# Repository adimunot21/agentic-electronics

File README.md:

# agentic-electronics

An experiment in letting an AI agent change an electronic circuit design, while an independent checker decides whether each change is accepted.

The agent proposes small edits to a parts list. It never judges its own work. A separate evaluator re-runs the real simulations (ngspice, KiCad) on the edited design and accepts or rejects the change against a policy written beforehand. The test circuit is an analog anti-aliasing filter in front of a 12-bit ADC.

This is research code. Nothing here is a board ready to manufacture.

## Status

Newest first. New entries are added on top; old entries are not rewritten.

* **2026-11-21. improve-live-12: ACCEPTED (v4).** After two honest no-improvement declarations the agent submitted one design that the independent evaluator accepted for the objective (alias -58.74 -> -59.58 dB, no policy violations; E96/E24 values, part numbers still unverified, REQ-STAB/REQ-BOM failures pre-existing). One accepted run in four on v4; advisory aids were visible (docs sections 25-26).
* **2026-11-21. improve-live-10 and v4 attainability.** Run 10 declared no improvement after reading its own previews (honest, not accepted). An offline search showed policy v4 is attainable (designs withheld from the repo). The advisory sanity check now also predicts REQ-BIAS; digest superseded with proof (docs sections 23-24).
* **2026-11-21. improve-live-9: no evaluation.** The agent spent all 45 model calls on 21 patches and 17 free sanity checks and never submitted (a usage limit hit mid-run and the new supervisor resumed it). Not accepted. Fix: the agent now sees its call budget in every reply; acceptance and policies unchanged. Digest superseded with proof (docs section 22).
* **2026-11-21. Pre-trial freeze.** README task labels, restoration-mode check list and E96 alias coverage for the advisory sanity check are done; trusted digest superseded with proof (docs section 21). Next: a live v4 trial under the hardened harness.
* **2026-11-20. Second-circuit groundwork.** A circuit-profile seam lets a second task be added by data (FE-AAF-001 behaviour unchanged), a supervisor resumes runs after provider usage limits, advisory edit-sanity is validated on 11 real designs, and a capacitor orderability table exists. A second-circuit contract is only a draft awaiting owner approval and is not published.
* **2026-11-20. Backlog 1-3 shipped by a five-agent hierarchy.** Provider usage limits are now their own stop reason (reset time recorded, preview budget kept across resume, `--wait-until-reset`); one combined preview covers corners plus guarded nominal metrics; an advisory edit-sanity check predicts corner gain before an evaluation is spent. Orderability research is partial (capacitor ranges unsourced). 346 unit + 14 integration tests pass; trusted digest superseded with proof (docs section 18).
* **2026-11-20. Public CI fixed.** The integration job had been failing since the first public push because the tool containers run as user 1000 and a GitHub runner is user 1001, so they could not write to the checkout. The repository now opens its own work directories for the containers; the latest run on `main` is green (unit and integration). New trusted digest recorded in the docs.
* **2026-11-20. Eighth live run: two evaluations, both rejected, then my subscription's usage limit.** The model found a design inside every corner limit with 0.54 dB of improvement (target 0.5), but a bias-margin rule it had not previewed rejected it; its repair broke the gain window. Runs 7 and 8 were cut short by the plan limit as much as by the design problem. Next on the backlog: handle provider limits automatically, and preview all guarded metrics together.
* **2026-11-20. Seventh live run (fourth task version): no evaluation reached, nothing accepted.** The new standard-values check worked (the model was refused four times for non-standard resistor values and adapted), but the run was interrupted by my subscription's usage limit, resumed once, and then stopped on three scattered malformed replies. The malformed-reply rule is now three in a row (twelve in total) instead of three in total. Tests pass (253 unit, 14 integration). New digest recorded in the docs.
* **2026-11-20. Orderable-values check added; fourth task version frozen.** The accepted design from run 6 used a resistor value (59.6k) that is not a standard 1% value, so it was not buildable. The edit checker can now refuse values outside the part's declared standard series (E96 resistors, E24 capacitors); task `improve-wide-retune-alias-v4` turns that on and is otherwise the same task. Tests pass (253 unit, 14 integration). New trusted digest recorded in the docs. No run on v4 yet.
* **2026-11-20. Fifth/sixth live runs: first acceptance on a task with no scripted answer** (`runs/agent/improve-live-6`; run 5 was lost to a provider timeout). The model used the worst-case and requirement previews, was rejected once for a tiny stability-metric increase, and was then accepted: worst-case stopband rejection improved by 1.0 dB (target 0.5 dB) by changing two parts (R1 59k to 59.6k, C1 18n to 20n). The run was interrupted by my subscription's 5-hour usage limit and resumed once. Limits: the new values are not orderable as far as I could check (59.6k is not a standard 1% value, and neither part number was found at the distributor searched), so this is not a buildable design; REQ-STAB is still failed; one task, advisory previews used, model may know this circuit class.
* **2026-11-20. Fourth live run: closest so far, nothing accepted** (`runs/agent/improve-live-4`). With the new worst-case preview the model found designs that beat the 0.5 dB target by about 1.8 dB inside every tolerance corner, but the stability check (REQ-STAB, which must not get worse) rejected both submissions, and the run hit its 30-call cap before the model could act on the second rejection. Added a second advisory preview that shows the nominal value of every requirement, including REQ-STAB, before a submission. Tests pass (218 unit, 14 integration). One run, one task.
* **2026-11-20. Harness milestones 1 and 2 landed; no new live run yet.** Duplicates and no-ops are now detected by the circuit's electrical content, not by file bytes, so a reverted design costs no evaluation and legitimate reverts no longer trip a stop rule. Cycling is bounded by design state. An agent can declare that it found no improvement and end the run without spending an evaluation. In improvement tasks the agent can now preview the evaluator's own worst-case sweep before submitting (advisory only; the evaluator still decides). Tests pass (217 unit, 13 integration). The improve-live-3 failure is replayed as a fixture. Two reviews by independent agents found no blockers. New trusted digest recorded in the docs.
* **2026-11-19. Third live run finished, nothing accepted** (`runs/agent/improve-live-3`, task `improve-wide-retune-alias-v3`). The model tried four small retunes using only the fast nominal check, judged each too risky for the worst-case limits, reverted them, and submitted what was electrically the original design. That cost one full evaluation and was rejected as no improvement; the agent did read the rejection. The run then ended on the harness rule against repeating an identical patch (two legitimate reverts looked identical), with 1 of 3 evaluations and 17 of 20 model calls used. One run, one task. Two harness flaws showed up and are not yet fixed: an electrically unchanged design can slip past the unchanged-design check, and the repeat-patch rule misfires on reverts.
* **2026-11-19. Feedback loop fixed; third task version frozen, not yet run.** After the second run, the harness now shows the agent a rejection's failing values and limits before it can stop the run, refuses unchanged or repeated designs without spending an evaluation, and judges progress by objective movement plus feasibility instead of counting violations. Task `improve-wide-retune-alias-v3` is the same task and rules as before, with one added sentence in what the agent is told: the score is the worst case over all tolerance corners. Plumbing controls pass under the new trusted digest. No model has run on it.
* **2026-11-19. Second live run finished, nothing accepted** (`runs/agent/improve-live-2`, task `improve-wide-retune-alias`). The run stopped on the harness's no-progress rule after 2 of 3 allowed evaluations. The first submission was an unchanged design (rejected, no improvement). The second changed one capacitor and cut worst-case stopband gain by 0.92 dB, which beats the 0.5 dB target, but pushed the highest corner gain to 1.373 against a limit of 1.3645, so the evaluator rejected it. One run, one task. No claim beyond that.
* **2026-11-19. Second task frozen, not yet run** (`improve-wide-retune-alias`, policy sha256 `7a02c547…`). Same objective and rules as the first task, but all eight filter parts of both stages may be edited and the target is a 0.5 dB gain in worst-case stopband rejection. No scripted solution exists for it. Plumbing controls only have been run; no model has touched it.
* **2026-11-19. Second task not frozen.** I tried to design a second improvement task on different parts of the circuit. I could not argue from the equations that a meaningful improvement is reachable under the current rules, so no task was frozen. The reasoning is in [`docs/second-task-attainability.md`](docs/second-task-attainability.md). The two part numbers from the accepted change were looked up at distributors and look orderable; see [`evidence/candidate-verification-improve-live-1.yaml`](evidence/candidate-verification-improve-live-1.yaml). First public push of this repository.
* **2026-11-19. First live improvement run accepted** (`runs/agent/improve-live-1`). One run, one task. Details below.
* **2026-11-18. First live repair run accepted** (`runs/agent/dev-c1-live-1`). One run, one task. Details below.
* **Earlier.** Tool chain, reference design, evaluator and harness built. See the git history.

## What works today

1. **The harness and the evaluator.** A controller gives the model a small set of typed tools (read the design, run quick checks, propose a patch, submit). Patches may only edit allowed fields of allowed parts. On submit, the evaluator runs the full pipeline itself and compares against the policy. There are two modes: *restoration* (the repaired design must match the original measurements) and *improvement* (a changed design is accepted only if it beats a target fixed in advance and breaks no hard limit). The unit tests (172) and the real-tool integration tests pass at the current tree. A wrong repair, written as a scripted test case, is rejected by the evaluator on real simulation evidence.
2. **A live repair.** A component value in the design was deliberately corrupted (C1 written as 1 nF against a part number for 18 nF). The model found the mismatch with the tools, patched it, and the evaluator accepted the result: one evaluation, 6 model calls (`runs/agent/dev-c1-live-1/summary.json`).
3. **A live improvement.** The target was fixed in a policy file before any candidate was evaluated: lower the worst-case stopband gain from 19 kHz to 1 MHz by at least 0.25 dB, over all 1024 corners of the tolerance box the evaluator uses, without breaking the passband, gain or other limits. The model changed R4, R5 and C3. The evaluator measured an improvement of 0.27 dB (-58.74 dB to -59.01 dB) and accepted it for that objective: 10 model calls, one evaluation (`runs/agent/improve-live-1/`, decision in `evaluations/decision_01.json`).

The intended action boundary: the model has no file or shell access (the CLI is started with its tools off, with no settings sources or MCP servers, from an empty directory), it can only emit one JSON action per reply, and the controller rejects anything malformed or out of scope before it does anything. This is how it is meant to work and how the tests exercise it. I have not shown that it is isolated or secure.

## Known limits

* One accepted change on one task, once. This is not evidence of a general design ability.
* The final design in the improvement run is the same as one candidate I had written in a scripted search earlier in the repo, which the model could not see. I cannot tell whether that is independent derivation or coincidence.
* The stability check (REQ-STAB) fails on the baseline design. A revised version of it is proposed but not approved. The policy lets a candidate leave it failing but never worse.
* The parts list has unresolved items: the two connectors have no part number, and the model for startup, saturation and overload behaviour is not tested.
* The new part numbers (`RC0603FR-0718K7L`, `C0805C512J5GACTU`) are unverified candidates. A distributor lookup found matching listings but I read no datasheet and placed no order.
* Costs are the CLI's list-price estimates, not billing. The harness has no cumulative dollar cap.
* The Python harness and its evaluator are trusted code. Any change to them changes the "trusted-code digest" recorded in each decision.

## Run the tests

Needs Python 3.12 and [uv](https://docs.astral.sh/uv/).

```bash
uv sync
uv run pytest tests/unit -q                       # offline unit tests
./scripts/bootstrap.sh                            # pulls pinned docker images, downloads the TI op-amp model (hash-checked)
uv run pytest tests/integration -q -m integration # needs docker; runs real KiCad, ngspice and Freerouting
```

The integration tests need docker and the bootstrap step. The TI op-amp model is not in this repository (its licence is not stated), so a fresh clone cannot run the full pipeline until it has been downloaded. Running a model against the harness (`python -m ae.harness.run --provider claude-cli`) spends model usage: read [`docs/agent-improvement-mode.md`](docs/agent-improvement-mode.md) first.

## Layout

* `src/ae/` toolchain runner, KiCad schematic and netlist handling, SPICE suite, checks, release outputs.
* `src/ae/harness/` the agent harness: controller, tools, patch validation, evaluator, frozen task policies (`tasks/`).
* `designs/`, `requirements/`, `evidence/`, `models/`, `analysis/` the circuit, its contract, part evidence and model provenance.
* `tests/` unit and integration tests. `scripts/` helper scripts (including fixture runs; they are scripted, not model output).
* `runs/` saved evidence: reference runs and agent runs. Only small files are kept (trace, summary, decisions, patches, diffs). Bulk simulation output is ignored.
* `docs/` architecture, harness and improvement-mode notes, limitations ledger, decisions.

## More reading

[Harness](docs/agent-harness.md) - [Improvement mode, accounting and launch notes](docs/agent-improvement-mode.md) - [Limitations ledger](docs/limitations.md) - [Architecture](docs/architecture.md) - [Prior art](docs/prior-art.md) - [Roadmap](docs/agentic-roadmap.md)

## Licence and third-party material

No licence has been chosen yet, so by default all rights are reserved. KiCad libraries are CC-BY-SA-4.0 with a design exception, and Freerouting (GPL-3.0) is run as a separate process. The TI op-amp model is downloaded locally and never committed.

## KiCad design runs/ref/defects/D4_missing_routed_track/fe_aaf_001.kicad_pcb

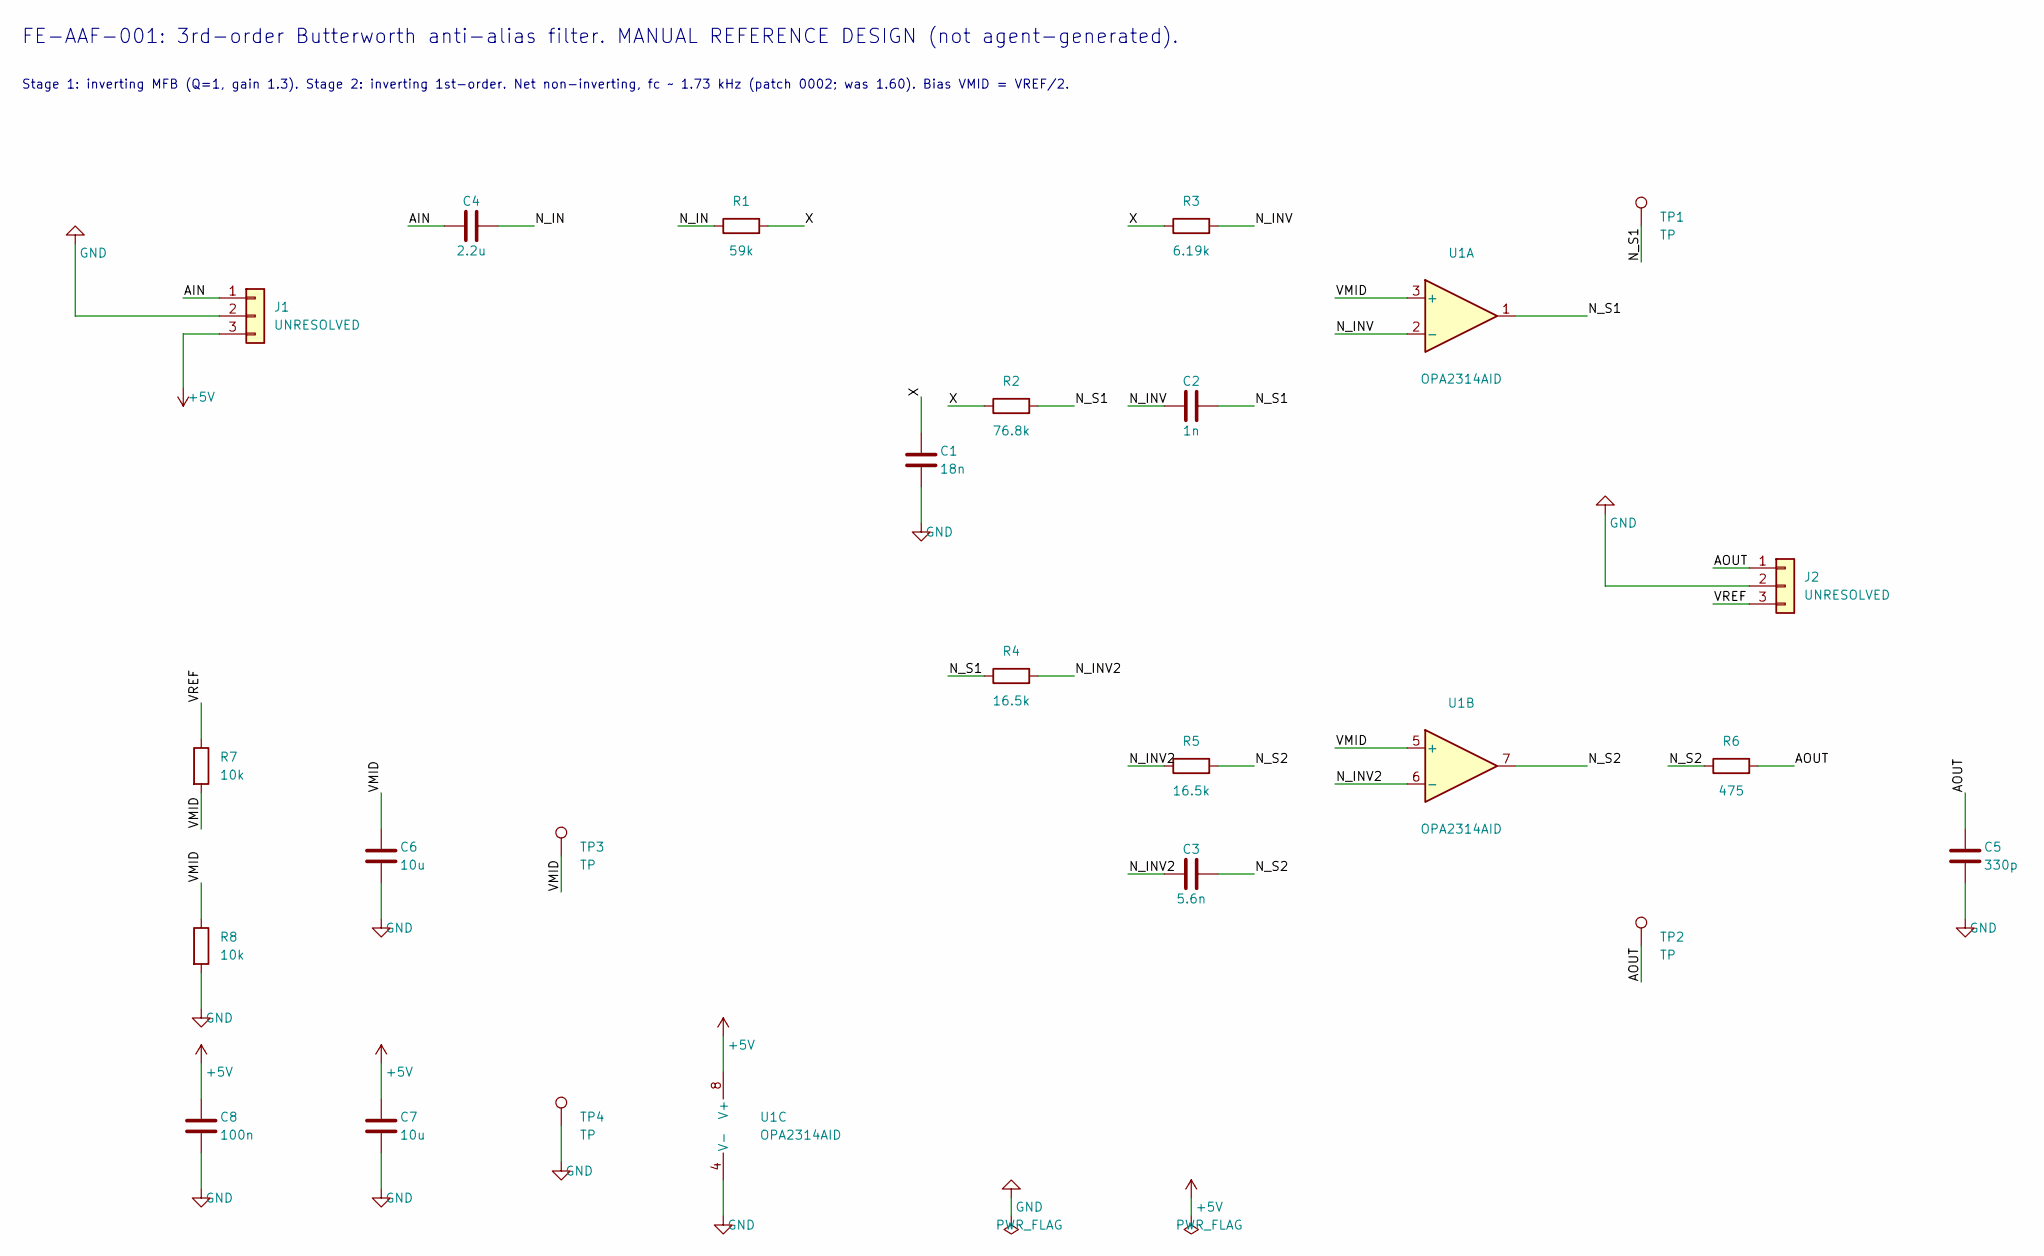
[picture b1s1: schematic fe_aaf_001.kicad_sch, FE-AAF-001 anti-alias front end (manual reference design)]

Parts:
C1: 18n; C_0805_2012Metric; Tolerance 5%; MPN C0805C183J5GACTU
C2: 1n; C_0805_2012Metric; Tolerance 5%; MPN C0805C102J5GACTU
C3: 5.6n; C_0805_2012Metric; Tolerance 5%; MPN C0805C562J5GACTU
C4: 2.2u; C_1206_3216Metric; Tolerance 20%; Voltage 16V; MPN C1206C225K4RACTU
C5: 330p; C_0805_2012Metric; Tolerance 5%; MPN C0805C331J5GACTU
C6, C7: 10u; C_1206_3216Metric; Tolerance 20%; Voltage 10V; MPN C1206C106K8RACTU
C8: 100n; C_0603_1608Metric; Tolerance 10%; Voltage 16V; MPN C0603C104K4RACTU
J1, J2: UNRESOLVED; PinHeader_1x03_P2.54mm_Vertical; MPN UNRESOLVED
R1: 59k; R_0603_1608Metric; Tolerance 1%; MPN RC0603FR-0759KL
R2: 76.8k; R_0603_1608Metric; Tolerance 1%; MPN RC0603FR-0776K8L
R3: 6.19k; R_0603_1608Metric; Tolerance 1%; MPN RC0603FR-076K19L
R4, R5: 16.5k; R_0603_1608Metric; Tolerance 1%; MPN RC0603FR-0716K5L
R6: 475; R_0603_1608Metric; Tolerance 1%; MPN RC0603FR-07475RL
R7, R8: 10k; R_0603_1608Metric; Tolerance 0.1%; MPN RT0603BRD0710KL
TP1, TP2, TP3, TP4: TP; TestPoint_Pad_D1.5mm; MPN no part (bare pad)
U1: OPA2314AID; SOIC-8_3.9x4.9mm_P1.27mm; MPN OPA2314AID

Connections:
+5V: C7.1, C8.1, J1.3, U1.8 (V+)
/AIN: C4.1, J1.1
/AOUT: C5.1, J2.1, R6.2, TP2.1
/N_IN: C4.2, R1.1
/N_INV: C2.1, R3.2, U1.2 (-)
/N_INV2: C3.1, R4.2, R5.1, U1.6 (-)
/N_S1: C2.2, R2.2, R4.1, TP1.1, U1.1
/N_S2: C3.2, R5.2, R6.1, U1.7
/VMID: C6.1, R7.2, R8.1, TP3.1, U1.3 (+), U1.5 (+)
/VREF: J2.3, R7.1
/X: C1.1, R1.2, R2.1, R3.1
GND: C1.2, C5.2, C6.2, C7.2, C8.2, J1.2, J2.2, R8.2, TP4.1, U1.4 (V-)

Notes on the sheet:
FE-AAF-001: 3rd-order Butterworth anti-alias filter. MANUAL REFERENCE DESIGN (not agent-generated).
Stage 1: inverting MFB (Q=1, gain 1.3). Stage 2: inverting 1st-order. Net non-inverting, fc ~ 1.73 kHz (patch 0002; was 1.60). Bias VMID = VREF/2.

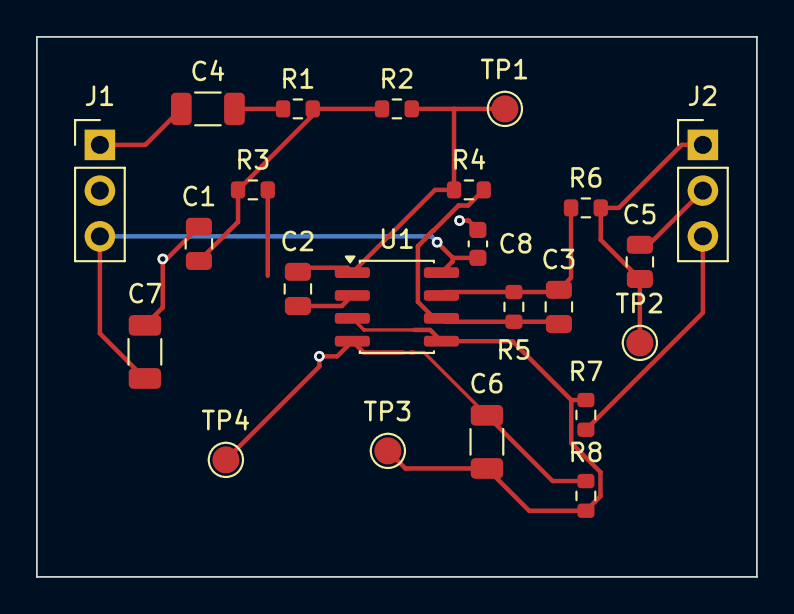
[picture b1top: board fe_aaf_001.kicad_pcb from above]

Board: 2 copper layers, 40.0 x 30.0 mm, 23 parts (0 on the bottom side), 12 nets.

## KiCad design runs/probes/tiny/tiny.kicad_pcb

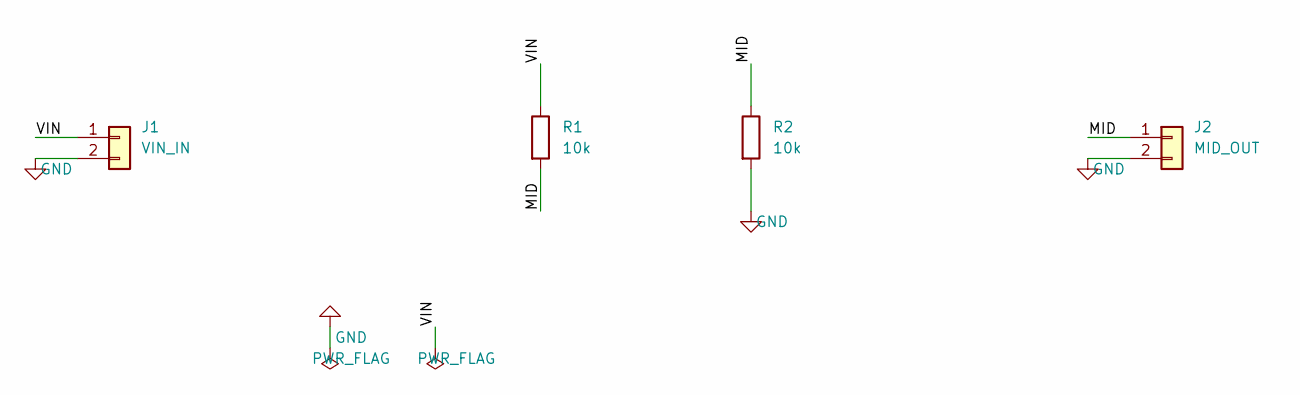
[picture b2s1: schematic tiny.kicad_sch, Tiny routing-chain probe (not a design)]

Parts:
J1: VIN_IN; PinHeader_1x02_P2.54mm_Vertical
J2: MID_OUT; PinHeader_1x02_P2.54mm_Vertical
R1, R2: 10k; R_0603_1608Metric

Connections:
/MID: J2.1, R1.2, R2.1
/VIN: J1.1, R1.1
GND: J1.2, J2.2, R2.2

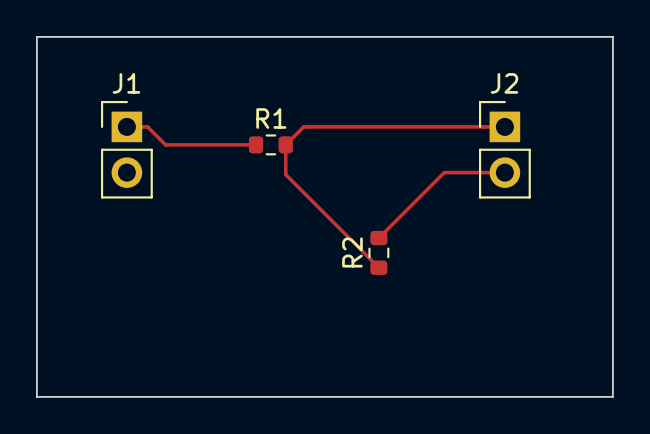
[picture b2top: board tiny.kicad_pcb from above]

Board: 2 copper layers, 32.0 x 20.0 mm, 4 parts (0 on the bottom side), 3 nets.
